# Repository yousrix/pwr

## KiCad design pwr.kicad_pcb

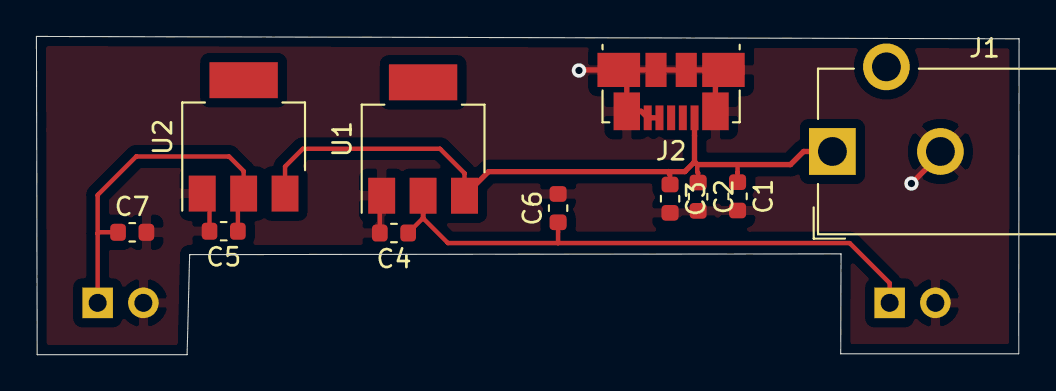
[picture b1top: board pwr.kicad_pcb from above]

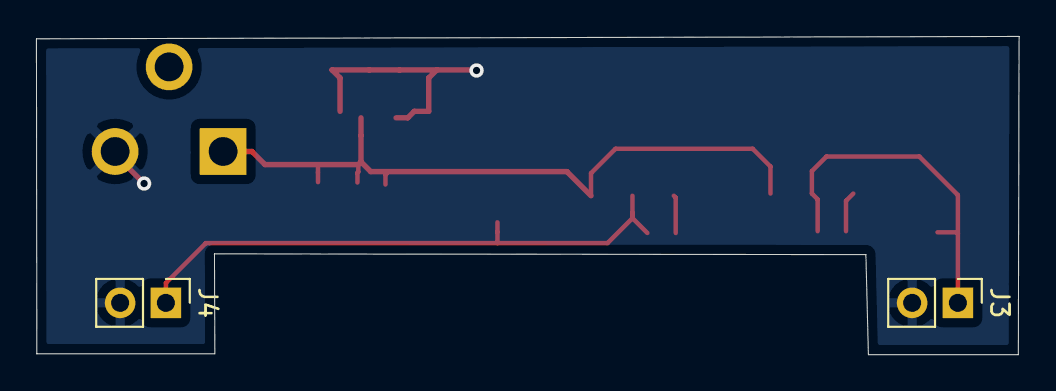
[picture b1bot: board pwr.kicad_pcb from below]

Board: 2 copper layers, 54.6 x 17.7 mm, 13 parts (2 on the bottom side), 4 nets.

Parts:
C1, C2, C3, C4, C5, C6, C7: 22uf; C_0603_1608Metric
J1: Jack-DC; BarrelJack_CUI_PJ-102AH_Horizontal
J2: USB_B_Micro; USB_Micro-B_Molex_47346-0001
J3, J4: Conn_01x02; PinHeader_1x02_P2.54mm_Vertical
U1: LD1117S50TR_SOT223; SOT-223-3_TabPin2
U2: LD1117S33TR_SOT223; SOT-223-3_TabPin2

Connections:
GND: C1.2, C2.2, C3.2, C4.2, C5.2, C6.2, C7.2, J1.2, J2.4, J2.5, J2.6, J3.2, J4.2, U1.1, U2.1
unnamed: C1.1, C2.1, C3.1, J1.1, J2.1, U1.3, U2.3
unnamed: C4.1, C6.1, J4.1, U1.2
unnamed: C5.1, C7.1, J3.1, U2.2
